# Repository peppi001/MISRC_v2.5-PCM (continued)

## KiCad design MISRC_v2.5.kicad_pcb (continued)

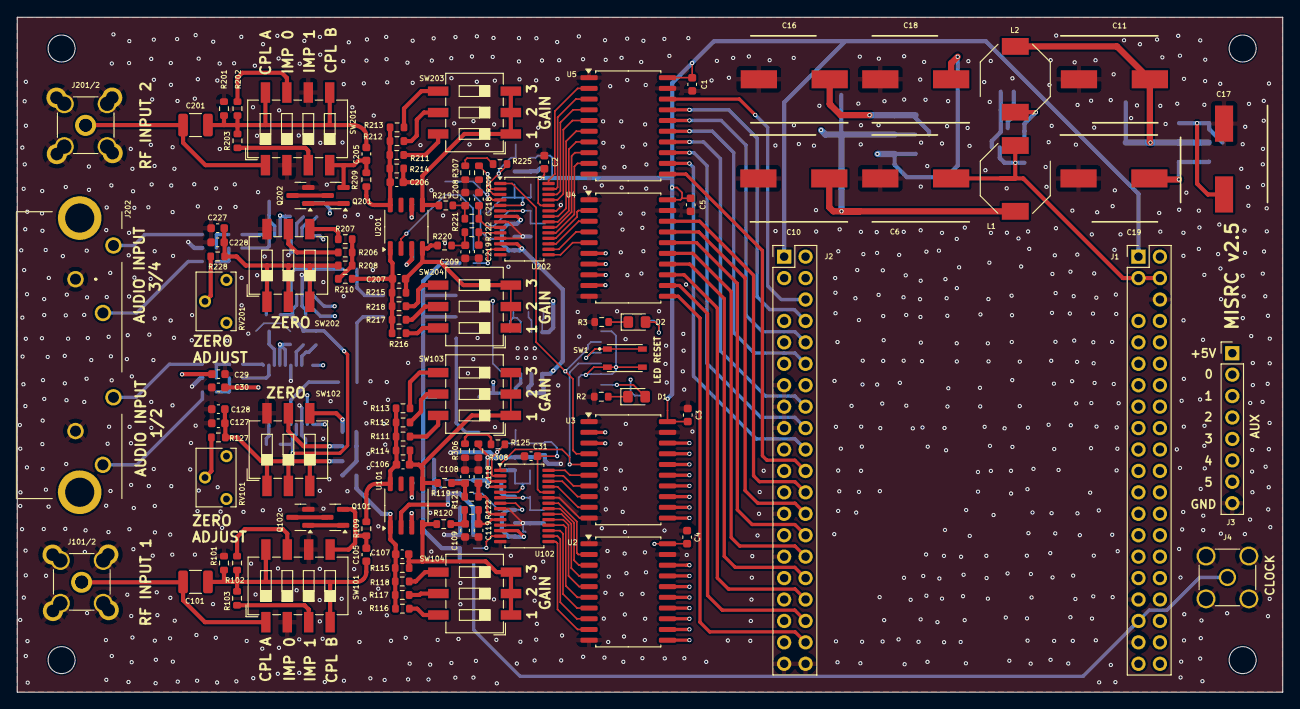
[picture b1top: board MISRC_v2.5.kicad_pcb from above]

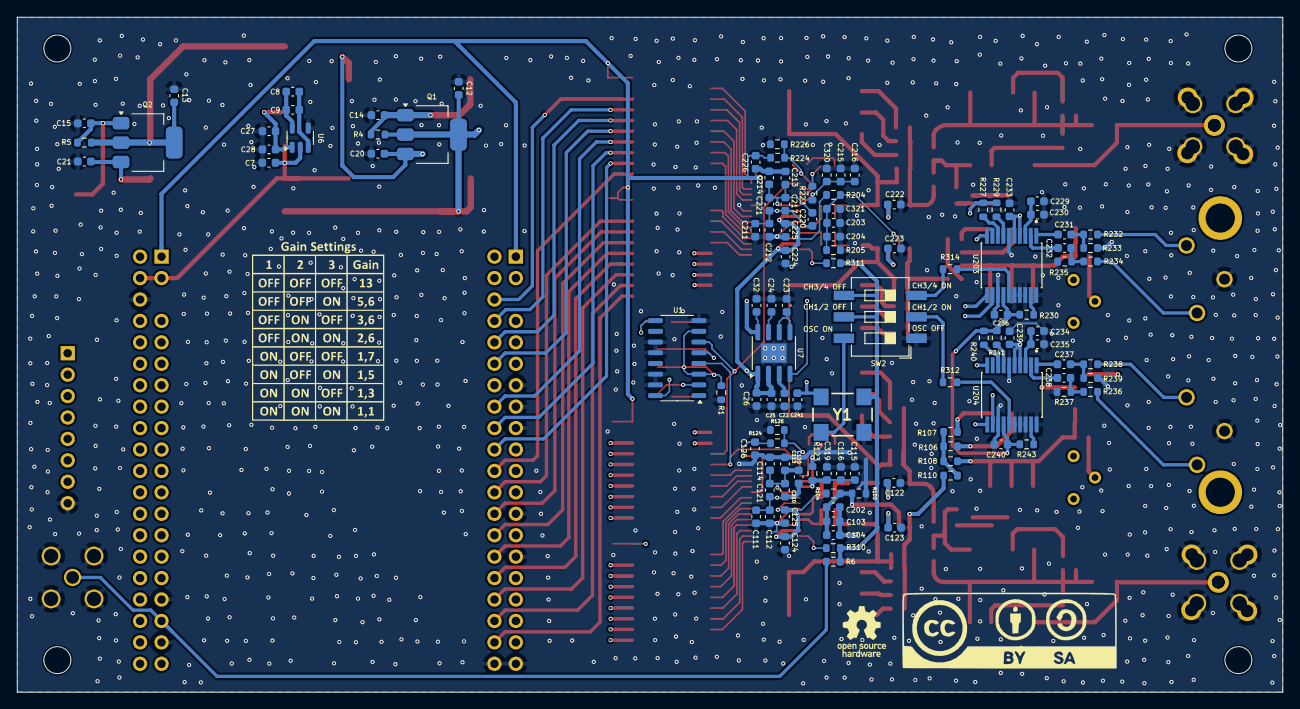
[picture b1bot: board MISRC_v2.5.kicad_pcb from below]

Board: 4 copper layers, 150.0 x 80.0 mm, 235 parts (114 on the bottom side), 180 nets.

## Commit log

2025-03-14 Tang Nano20k 3D model
